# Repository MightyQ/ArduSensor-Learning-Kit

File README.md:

ArduSensor-Learning-Kit
=======================

Collaboration with SparkFun Electronics - a pack of 8 ArduSensors with 1 ArduSensor Shield

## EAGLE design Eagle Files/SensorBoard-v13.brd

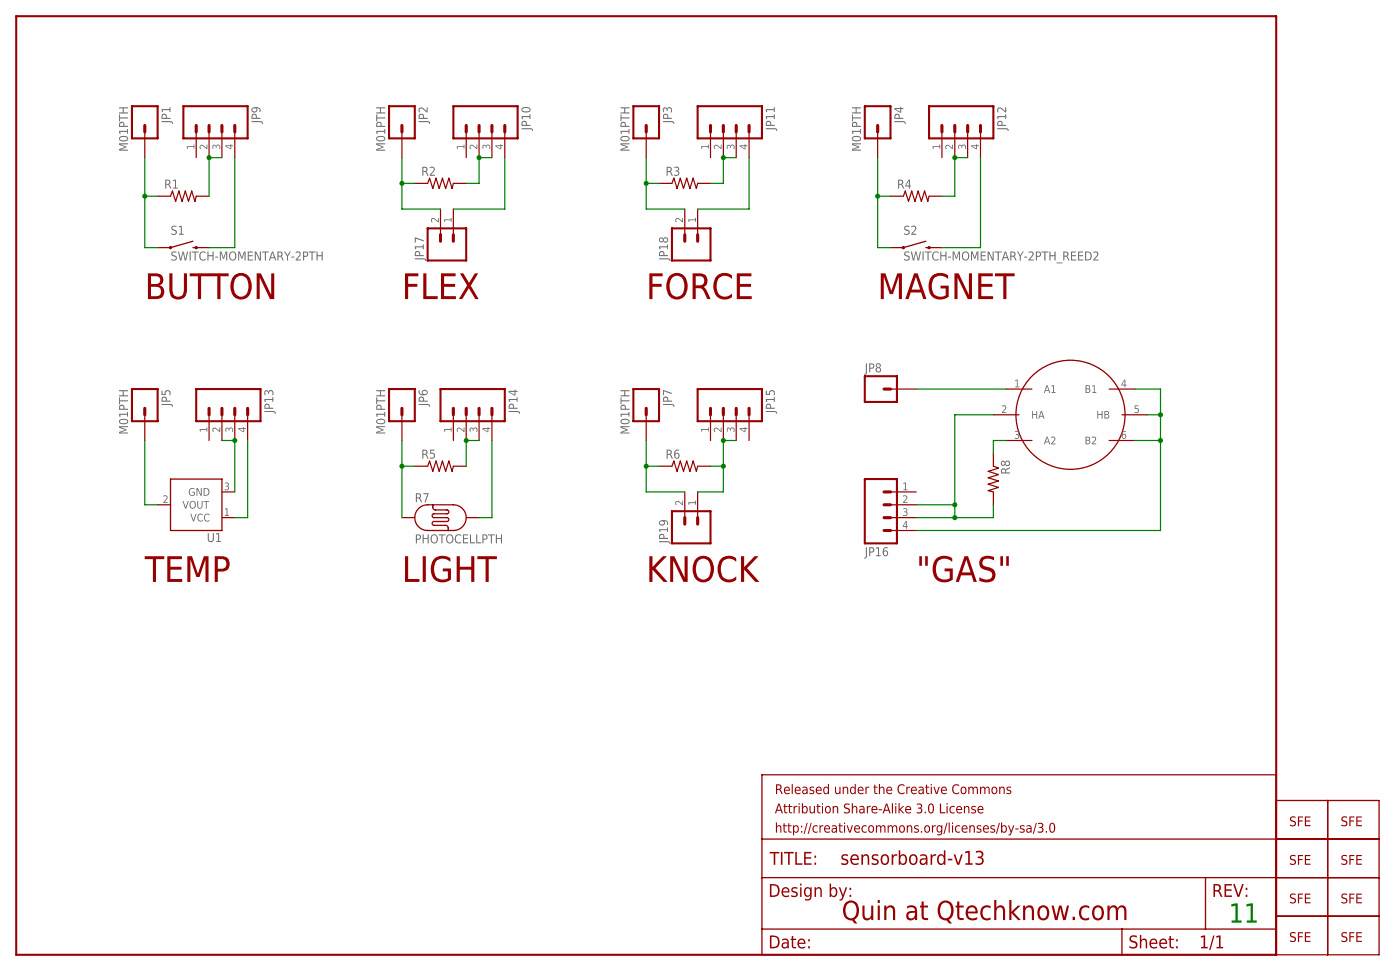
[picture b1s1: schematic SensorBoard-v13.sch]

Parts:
FRAME1: FRAME-LETTER; CREATIVE_COMMONS
JP1, JP2, JP3, JP4, JP5, JP6, JP7, JP8: M01PTH; 1X01
JP9, JP10, JP11, JP12, JP13, JP14, JP15, JP16: M04PTH; 1X04
JP17, JP18, JP19: M02PTH; 1X02
LOGO1, LOGO2, LOGO3, LOGO4, LOGO5, LOGO6, LOGO7, LOGO8: LOGO-SFESK; SFE-LOGO-FLAME
R1, R2, R3, R4, R5, R6, R8: RESISTORAXIAL-0.3; AXIAL-0.3
R7: PHOTOCELLPTH; PHOTOCELL
S1: SWITCH-MOMENTARY-2PTH; TACTILE-PTH
S2: SWITCH-MOMENTARY-2PTH_REED2; REED_SWITCH_PLASTIC
U1: TMP36GT9; TO-92
U$1: GAS-SENSORNEW; GAS_SENSOR

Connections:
1_N$1: JP8.1, U$1.1 (A1)
1_N$2: JP16.4, U$1.4 (B1), U$1.5 (HB), U$1.6 (B2)
1_N$3: JP16.2, JP16.3, R8.P$2 (2), U$1.2 (HA)
1_N$4: R8.P$1 (1), U$1.3 (A2)
2_1_N$1: JP1.1, R1.P$1 (1), S1.1
2_1_N$2: JP9.2, JP9.3, R1.P$2 (2)
2_1_N$3: JP9.4, S1.3 (2)
2_2_N$1: JP2.1, JP17.2, R2.P$1 (1)
2_2_N$2: JP10.2, JP10.3, R2.P$2 (2)
2_2_N$3: JP10.4, JP17.1
2_3_N$1: JP3.1, JP18.2, R3.P$1 (1)
2_3_N$2: JP11.2, JP11.3, R3.P$2 (2)
2_3_N$3: JP11.4, JP18.1
2_4_N$1: JP7.1, JP19.2, R6.P$1 (1)
2_4_N$2: JP15.2, JP15.3, JP19.1, R6.P$2 (2)
2_5_N$1: JP6.1, R5.P$1 (1), R7.1
2_5_N$2: JP14.2, JP14.3, R5.P$2 (2)
2_5_N$3: JP14.4, R7.2
2_6_N$1: JP4.1, R4.P$1 (1), S2.P$1 (1)
2_6_N$2: JP12.2, JP12.3, R4.P$2 (2)
2_6_N$3: JP12.4, S2.P$2 (2)
2_7_N$1: JP5.1, U1.2 (VOUT)
2_7_N$2: JP13.2, JP13.3, U1.3 (GND)
2_7_N$3: JP13.4, U1.1 (VCC)

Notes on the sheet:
FLEX
FORCE
MAGNET
TEMP
LIGHT
KNOCK
"GAS"
BUTTON
Quin at Qtechknow.com

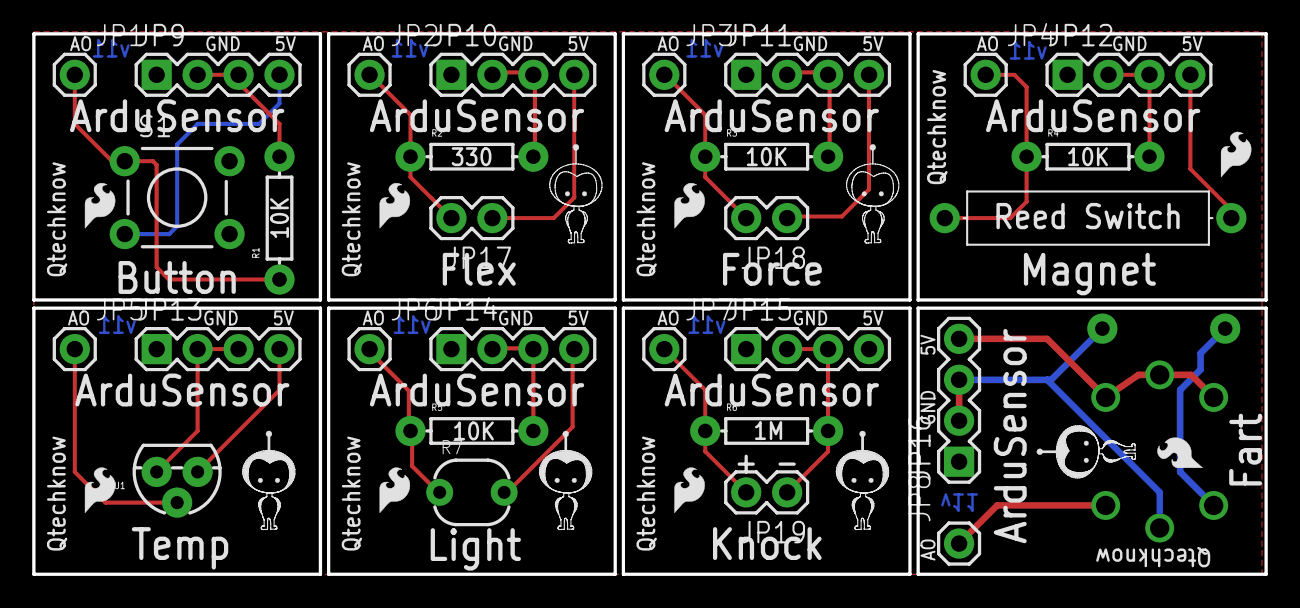
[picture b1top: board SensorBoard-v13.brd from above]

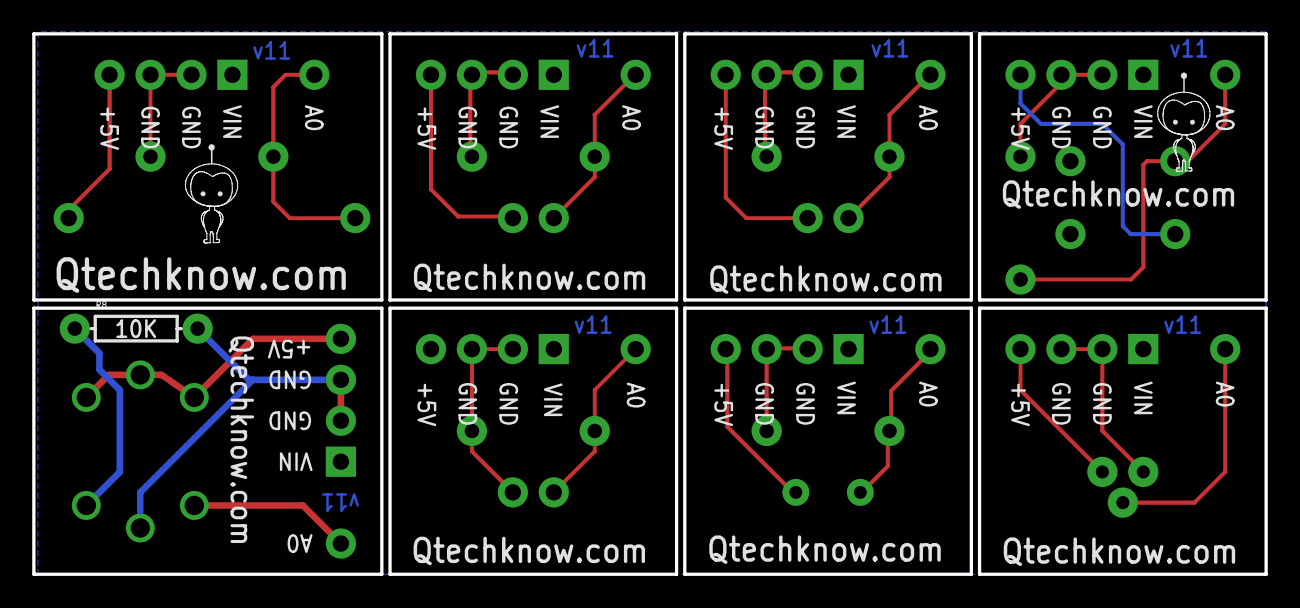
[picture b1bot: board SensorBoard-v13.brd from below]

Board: 2 copper layers, 76.5 x 33.5 mm, 48 parts (3 on the bottom side), 24 nets.

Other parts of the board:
U$2, U$3, U$4, U$6: LOGO-SMALL-FILL-SILK
U$5, U$21, U$22, U$23: MIGHTYQ-S-SILK; LOGO-SMALL-SILK

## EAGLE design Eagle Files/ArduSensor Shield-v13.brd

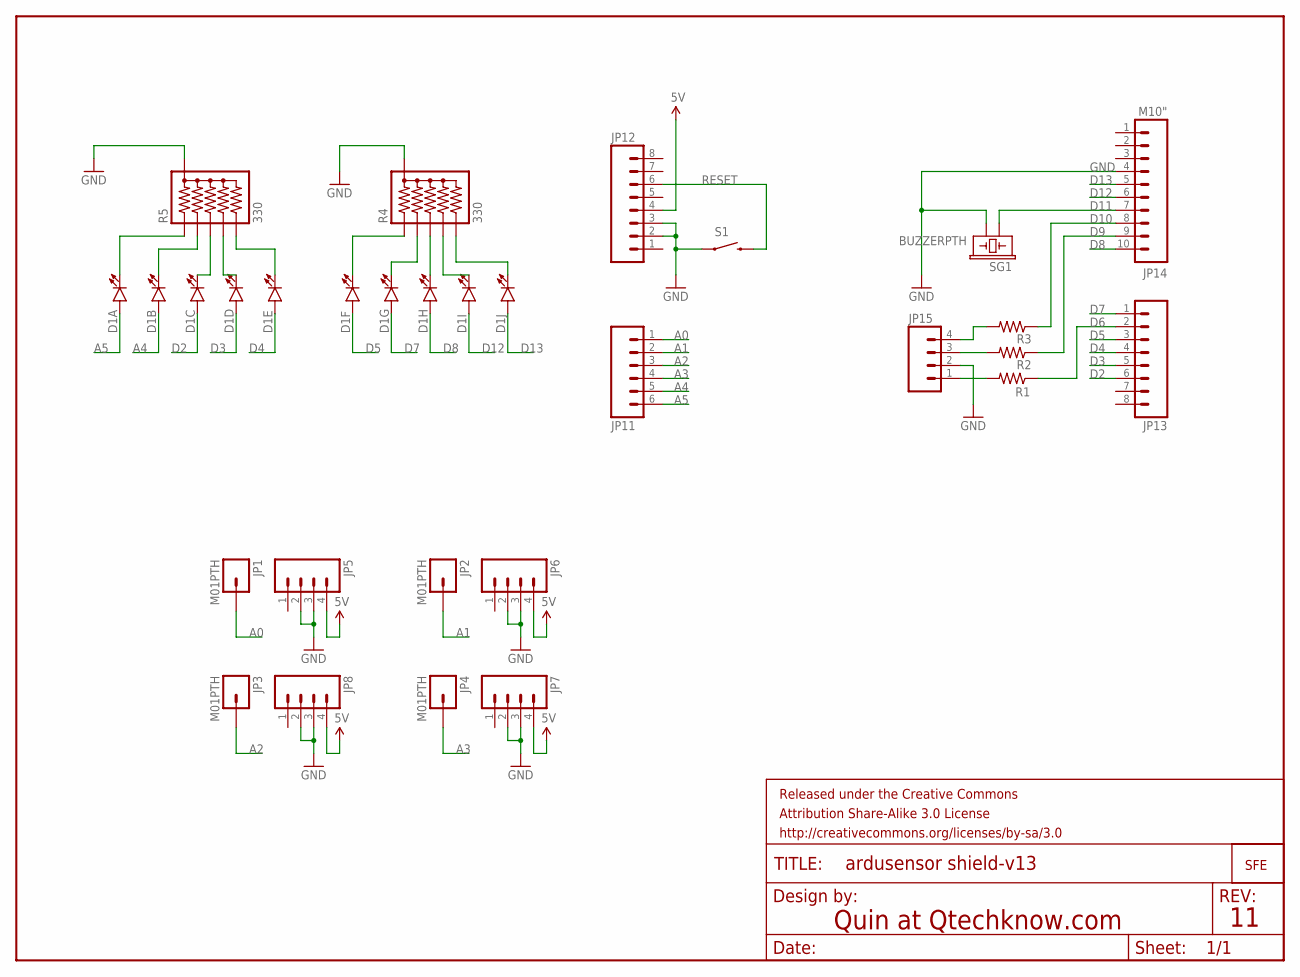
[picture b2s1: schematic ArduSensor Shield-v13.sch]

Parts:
D1: LED_BARGRAPH_10; LED_BARGAPH_10
FRAME1: FRAME-LETTER; CREATIVE_COMMONS
JP1, JP2, JP3, JP4: M01PTH; 1X01
JP5, JP6, JP7, JP8, JP15: M04PTH; 1X04
JP9: LOGO-SFENEW; SFE-NEW-WEBLOGO
JP11: M06SIP; 1X06
JP12, JP13: M081X08; 1X08
JP14: M10"; 1X10
R1, R2, R3: RESISTORPTH-1/6W; 1/6W-RES
R4, R5: 330; RPACK-SIP-PTH-5
S1: SWITCH-MOMENTARY-2PTH; TACTILE-PTH
SG1: BUZZERPTH; BUZZER-12MM

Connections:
5V: JP5.4, JP6.4, JP7.4, JP8.4, JP12.4
A0: JP1.1, JP11.1
A1: JP2.1, JP11.2
A2: JP3.1, JP11.3
A3: JP4.1, JP11.4
A4: D1.2 (A), JP11.5
A5: D1.1 (A), JP11.6
D2: D1.3 (A), JP13.6
D3: D1.4 (A), JP13.5
D4: D1.5 (A), JP13.4
D5: D1.6 (A), JP13.3
D6: JP13.2, R1.1
D7: D1.7 (A), JP13.1
D8: D1.8 (A), JP14.10
D9: JP14.9, R2.1
D10: JP14.8, R3.1
D11: JP14.7, SG1.+ (1)
D12: D1.9 (A), JP14.6
D13: D1.10 (A), JP14.5
GND: JP5.2, JP5.3, JP6.2, JP6.3, JP7.2, JP7.3, JP8.2, JP8.3, JP12.2, JP12.3, JP14.4, JP15.2, R4.P$1 (1), R5.P$1 (1), S1.1, SG1.- (2)
unnamed: JP15.1, R1.2
unnamed: JP15.3, R2.2
unnamed: JP15.4, R3.2
unnamed: D1.11 (C), R4.P$6 (6)
unnamed: D1.12 (C), R4.P$5 (5)
unnamed: D1.13 (C), R4.P$4 (4)
unnamed: D1.14 (C), R4.P$3 (3)
unnamed: D1.15 (C), R4.P$2 (2)
unnamed: D1.16 (C), R5.P$6 (6)
unnamed: D1.17 (C), R5.P$5 (5)
unnamed: D1.18 (C), R5.P$4 (4)
unnamed: D1.19 (C), R5.P$3 (3)
unnamed: D1.20 (C), R5.P$2 (2)
RESET: JP12.6, S1.3 (2)

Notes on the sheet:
Quin at Qtechknow.com

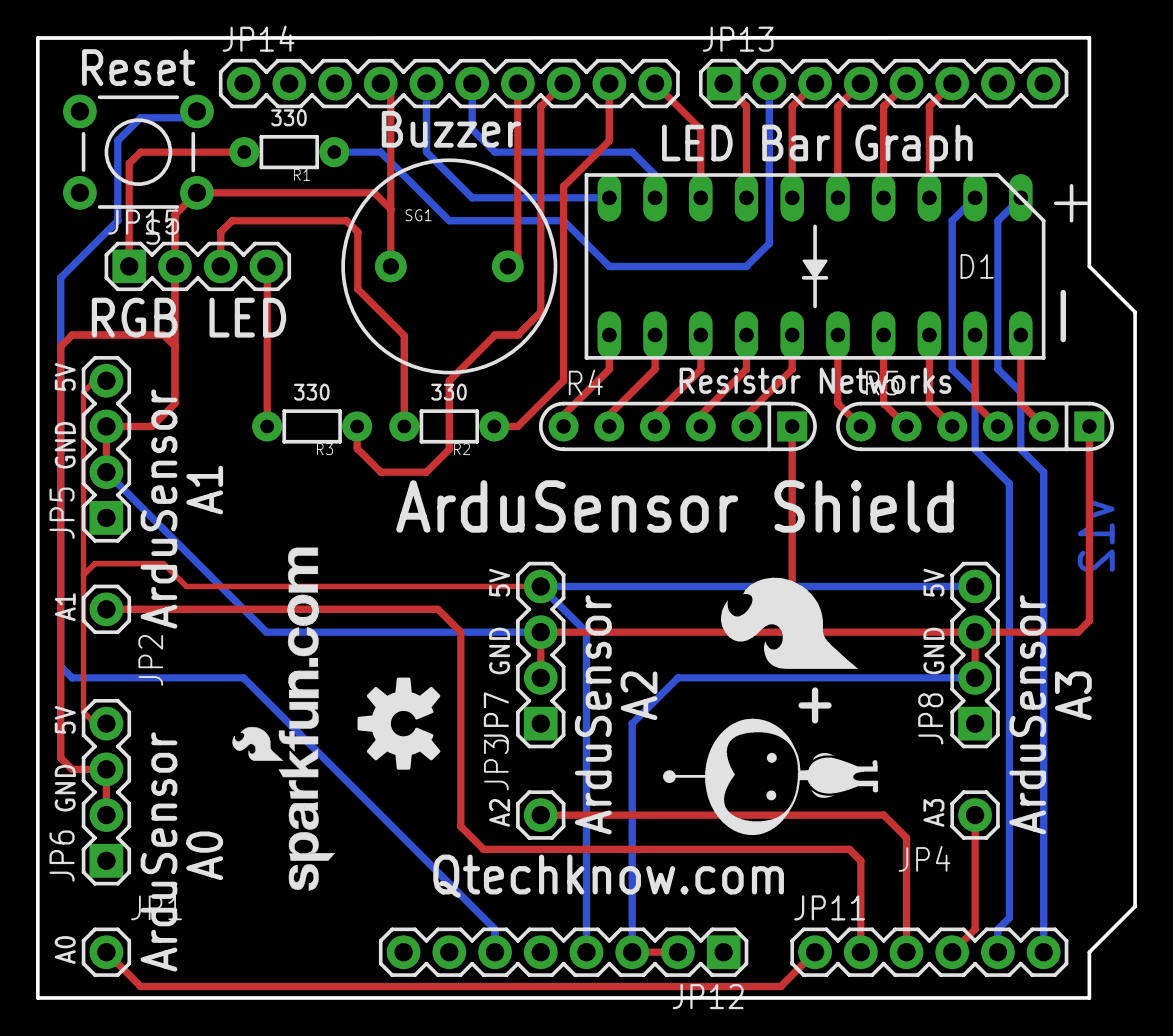
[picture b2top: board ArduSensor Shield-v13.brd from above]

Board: 2 copper layers, 61.0 x 53.3 mm, 27 parts (1 on the bottom side), 34 nets.

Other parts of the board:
U$6: SFE_LOGO_FLAME_.3
U$7: QTK_GUYBIG
U$8: OSHW-LOGO-M
U$10: QTK_GUYMEDIUM

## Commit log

2014-06-23 added new Eagle files
2014-06-23 fixed text and added OSHWA logo
2014-08-19 added better Qtechknow logo dude to the boards
2014-08-24 extras

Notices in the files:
parts and their libraries:
SFE LED: Licensing: CC v3.0 Share-Alike You are welcome to use this library for commercial purposes.
SparkFun-Aesthetics: Released under the Creative Commons Attribution Share-Alike 3.0 License
SparkFun-Aesthetics: http://creativecommons.org/licenses/by-sa/3.0
